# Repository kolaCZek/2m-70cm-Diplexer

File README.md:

# 2m/70cm Diplexer

[OSHPark Project](https://oshpark.com/shared_projects/0GlwsfHV)

## Characteristics

## BOM

 - 2x [1008 56nH](https://www.tme.eu/en/details/cw1008-56/smd-coils/ferrocore/)
 - 2x [1008 15nH](https://www.tme.eu/en/details/cw1008-15/smd-coils/ferrocore/)
 - 1x [1008 100nH](https://www.tme.eu/en/details/cw1008-100/smd-coils/ferrocore/)
 - 2x [0805 22pf](https://www.tme.eu/en/details/cl21c220jbannnc/0805-mlcc-smd-capacitors/samsung/)
 - 2x [0805 8.2pF](https://www.tme.eu/en/details/cl21c8r2cbannnc/0805-mlcc-smd-capacitors/samsung/)
 - 1x [0805 5.6pF](https://www.tme.eu/en/details/cl21c5r6cbaannc/0805-mlcc-smd-capacitors/samsung/)
 - 3x [SMA](https://www.ebay.com/sch/i.html?_from=R40&_sacat=0&_nkw=sma+female+pcb+edge+mount&rt=nc&LH_BIN=1)
 - 1x [PCB](https://oshpark.com/shared_projects/0GlwsfHV)

## Other Projects

 - [2m Band Pass Filter](https://github.com/kolaCZek/2m-Band-Pass-Filter)
 - [FM Trap](https://github.com/kolaCZek/FM-Trap)
 - [Bias-T](https://github.com/kolaCZek/Bias-T)

## License

[Apache License Version 2.0](./LICENSE)

## Donate

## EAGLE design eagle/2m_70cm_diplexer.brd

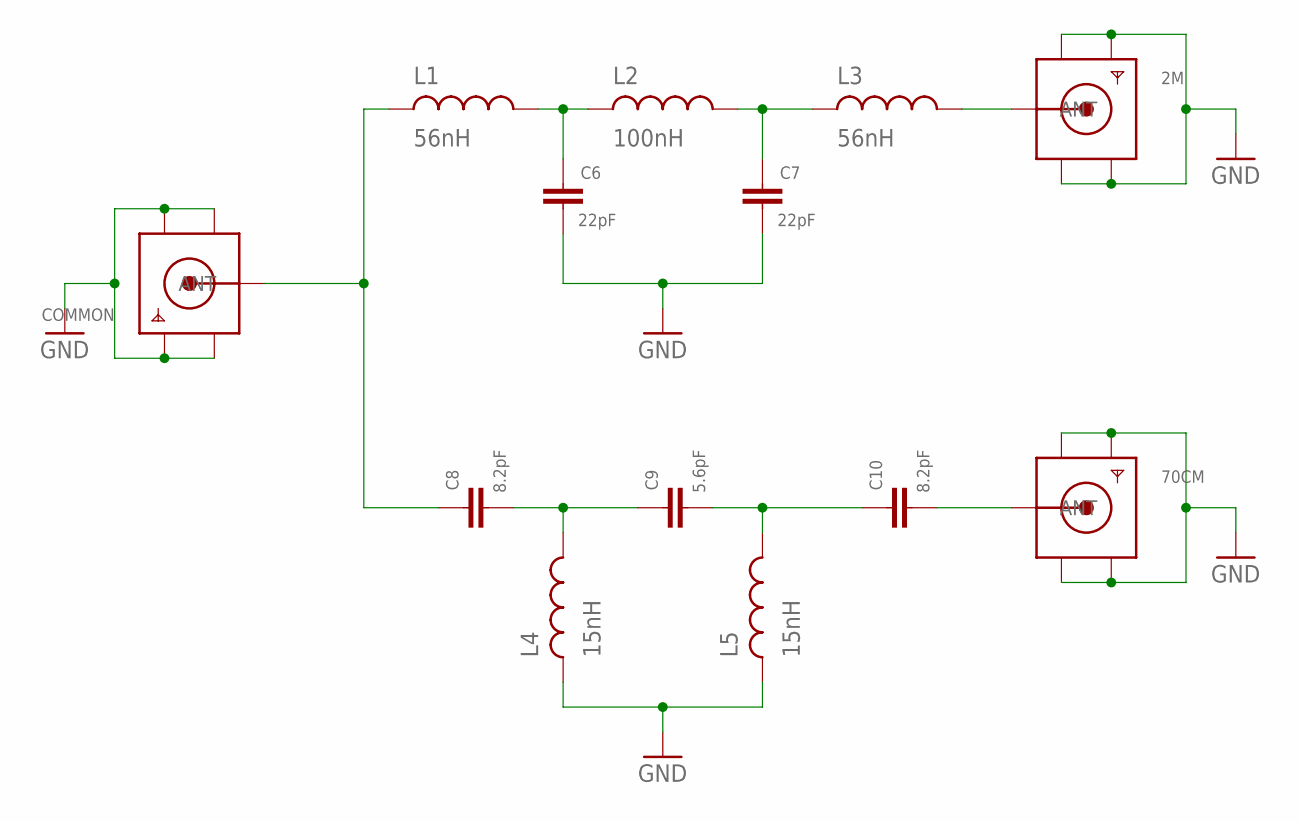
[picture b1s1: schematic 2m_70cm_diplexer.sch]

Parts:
2M, 70CM: SMACONNECTOR_EDGE; SMA_EDGELAUNCH
C6, C7: 22pF; 0805
C8, C10: 8.2pF; 0805
C9: 5.6pF; 0805
COMMON: SMACONNECTOR_EDGE; SMA_EDGELAUNCH
L1, L3: 56nH; 1008INDUCTOR
L2: 100nH; 1008INDUCTOR
L4, L5: 15nH; 1008INDUCTOR

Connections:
GND: 2M.GND@1 (GND4), 2M.GND@2 (GND3), 2M.GND@3 (GND2), 2M.GND@4 (GND1), 70CM.GND@1 (GND4), 70CM.GND@2 (GND3), 70CM.GND@3 (GND2), 70CM.GND@4 (GND1), C6.P$1, C7.P$1, COMMON.GND@1 (GND4), COMMON.GND@2 (GND3), COMMON.GND@3 (GND2), COMMON.GND@4 (GND1), L4.P$1, L5.P$1
L2: C7.P$2, L2.P$2, L3.P$1
unnamed: 2M.P (ANT), L3.P$2
unnamed: C6.P$2, L1.P$2, L2.P$1
unnamed: C8.P$1, C9.P$2, L4.P$2
unnamed: C9.P$1, C10.P$2, L5.P$2
unnamed: 70CM.P (ANT), C10.P$1
unnamed: C8.P$2, COMMON.P (ANT), L1.P$1

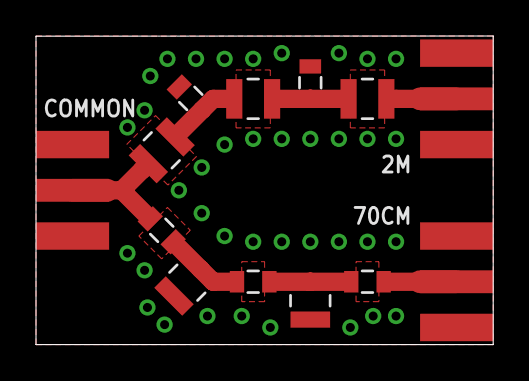
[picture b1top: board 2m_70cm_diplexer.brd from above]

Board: 2 copper layers, 25.4 x 17.1 mm, 13 parts (0 on the bottom side), 8 nets.

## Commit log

2018-02-15 Init commit
2018-02-15 Readme - Other projects
2022-01-25 Add Buy me coffe button
